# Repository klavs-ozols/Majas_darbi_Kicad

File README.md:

# Majas_darbi_Kicad
Šī ir mape, kur būs majasdarbi.

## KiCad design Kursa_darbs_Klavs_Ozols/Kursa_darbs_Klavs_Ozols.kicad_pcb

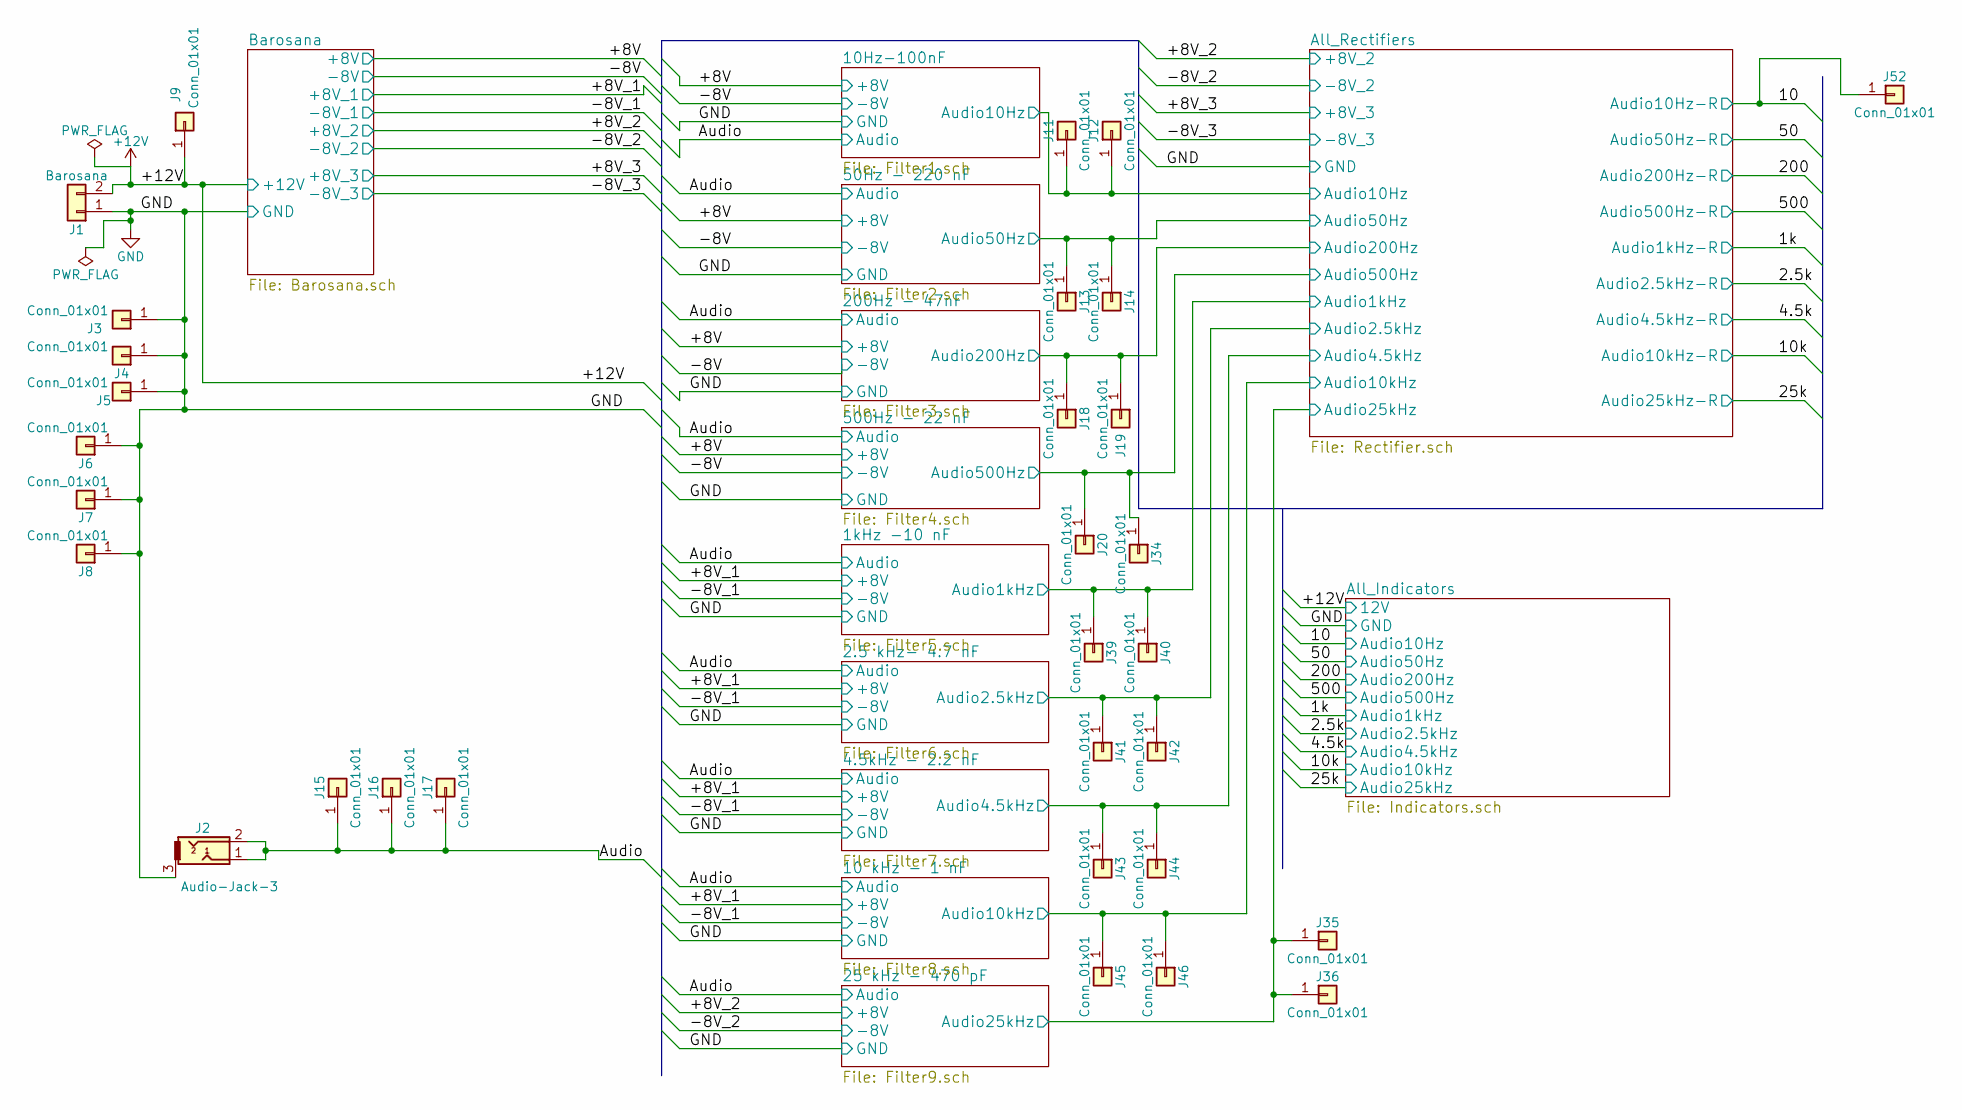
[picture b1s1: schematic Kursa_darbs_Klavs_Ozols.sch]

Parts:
J1: Barosana; BARREL_JACK
J2: Audio-Jack-3; Audio_Jack_3.5_mm_Stereo
J3, J4, J5, J6, J7, J8: Conn_01x01; MountingHole_3.2mm_M3_Pad_Via
J9, J11, J12, J13, J14, J15, J16, J17, J18, J19, J20, J34, J35, J36, J39, J40, J41, J42, J43, J44, J45, J46, J52: Conn_01x01; Measurement_Point_Round-TH_Small

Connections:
+12V: J1.2, J9.1; also elsewhere on the board
/1kHz -10 nF/Audio1kHz: J39.1, J40.1; also elsewhere on the board
/2.5 kHz- 4.7 nF/Audio2.5kHz: J41.1, J42.1; also elsewhere on the board
/4.5kHz - 2.2 nF/Audio4.5kHz: J43.1, J44.1; also elsewhere on the board
/10: J52.1; also elsewhere on the board
/10 kHz - 1 nF/Audio10kHz: J45.1, J46.1; also elsewhere on the board
/10Hz-100nF/Audio10Hz: J11.1, J12.1; also elsewhere on the board
/25 kHz - 470 pF/Audio25kHz: J35.1, J36.1; also elsewhere on the board
/50Hz - 220 nF/Audio50Hz: J13.1, J14.1; also elsewhere on the board
/200Hz - 47nF/Audio200Hz: J18.1, J19.1; also elsewhere on the board
/500Hz - 22 nF/Audio500Hz: J20.1, J34.1; also elsewhere on the board
/Audio: J2.1, J2.2, J15.1, J16.1, J17.1; also elsewhere on the board
GND: J1.1, J2.3, J3.1, J4.1, J5.1, J6.1, J7.1, J8.1; also elsewhere on the board

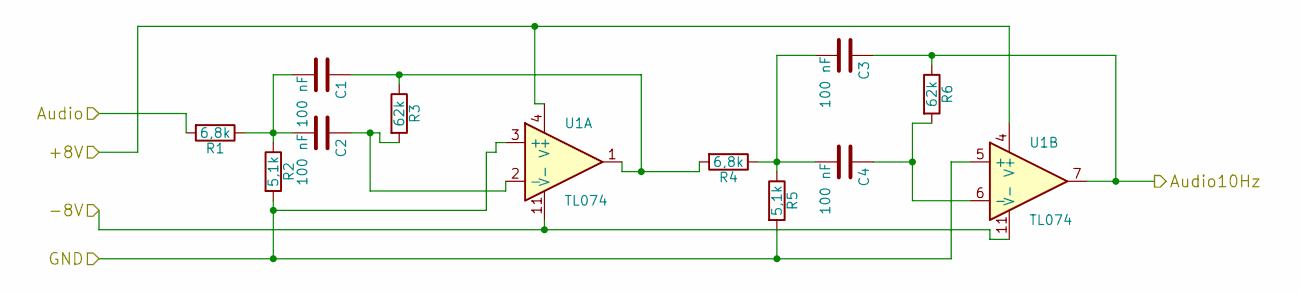
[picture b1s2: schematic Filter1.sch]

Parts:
C1, C2, C3, C4: 100 nF
R1, R4: 6,8k
R2, R5: 5,1k
R3, R6: 62k
U1: TL074

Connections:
/10Hz-100nF/Audio10Hz: C3.1, R6.1, U1.7; also elsewhere on the board
/+8V: U1.4 (V+); also elsewhere on the board
/-8V: U1.11 (V-); also elsewhere on the board
/Audio: R1.2; also elsewhere on the board
GND: R2.2, R5.2, U1.3 (+), U1.5 (+); also elsewhere on the board
unnamed: C1.1, R3.1, R4.2, U1.1
unnamed: C1.2, C2.2, R1.1, R2.1
unnamed: C2.1, R3.2, U1.2 (-)
unnamed: C3.2, C4.2, R4.1, R5.1
unnamed: C4.1, R6.2, U1.6 (-)

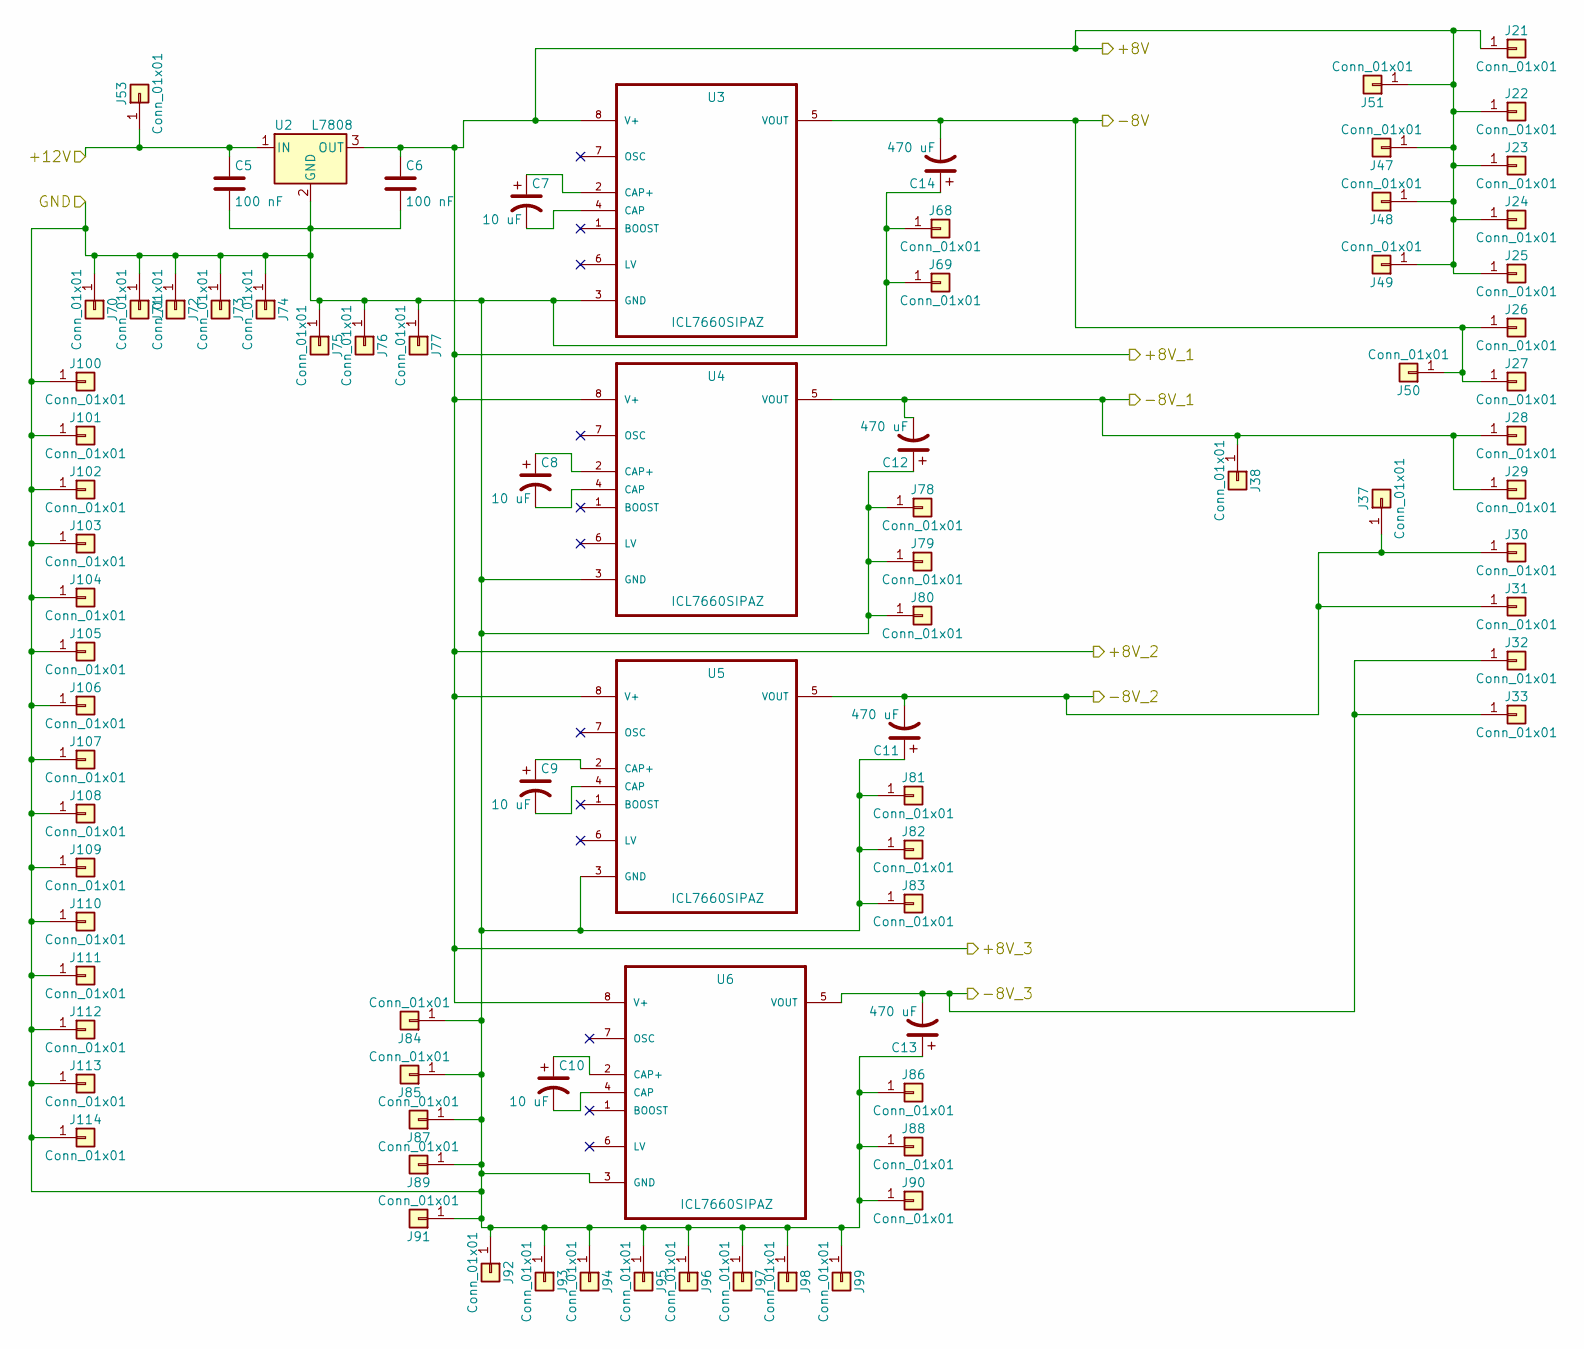
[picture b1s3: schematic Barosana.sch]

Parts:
C5, C6: 100 nF; C_1210_HandSoldering
C7, C8, C9, C10: 10 uF; CP_Elec_4x5.8
C11, C12, C13, C14: 470 uF; CP_Elec_10x10.5
J21, J22, J23, J24, J25, J26, J27, J28, J29, J30, J31, J32, J33, J37, J38, J47, J48, J49, J50, J51, J53, J68, J69, J70, J71, J72, J73, J74, J75, J76, J77, J78, J79, J80, J81, J82, J83, J84, J85, J86, J87, J88, J89, J90, J91, J92, J93, J94, J95, J96, J97, J98, J99, J100, J101, J102, J103, J104, J105, J106, J107, J108, J109, J110, J111, J112, J113, J114: Conn_01x01; Measurement_Point_Round-TH_Small
U2: L7808; TO-220_Vertical
U3, U4, U5, U6: ICL7660SIPAZ; SOIC-8_3.9x4.9mm_Pitch1.27mm

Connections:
+12V: C5.1, J53.1, U2.1 (IN); also elsewhere on the board
/+8V: C6.1, J21.1, J22.1, J23.1, J24.1, J25.1, J47.1, J48.1, J49.1, J51.1, U2.3 (OUT), U3.8 (V+), U4.8 (V+), U5.8 (V+), U6.8 (V+); also elsewhere on the board
/-8V: C14.2, J26.1, J27.1, J50.1, U3.5 (VOUT); also elsewhere on the board
/-8V_1: C12.2, J28.1, J29.1, J38.1, U4.5 (VOUT); also elsewhere on the board
GND: C5.2, C6.2, C11.1, C12.1, C13.1, C14.1, J68.1, J69.1, J70.1, J71.1, J72.1, J73.1, J74.1, J75.1, J76.1, J77.1, J78.1, J79.1, J80.1, J81.1, J82.1, J83.1, J84.1, J85.1, J86.1, J87.1, J88.1, J89.1, J90.1, J91.1, J92.1, J93.1, J94.1, J95.1, J96.1, J97.1, J98.1, J99.1, J100.1, J101.1, J102.1, J103.1, J104.1, J105.1, J106.1, J107.1, J108.1, J109.1, J110.1, J111.1, J112.1, J113.1, J114.1, U2.2 (GND), U3.3 (GND), U4.3 (GND), U5.3 (GND), U6.3 (GND); also elsewhere on the board
unnamed: C7.1, U3.2 (CAP+)
unnamed: C7.2, U3.4 (CAP)
unnamed: C8.1, U4.2 (CAP+)
unnamed: C8.2, U4.4 (CAP)
unnamed: C9.1, U5.2 (CAP+)
unnamed: C9.2, U5.4 (CAP)
unnamed: C10.1, U6.2 (CAP+)
unnamed: C10.2, U6.4 (CAP)

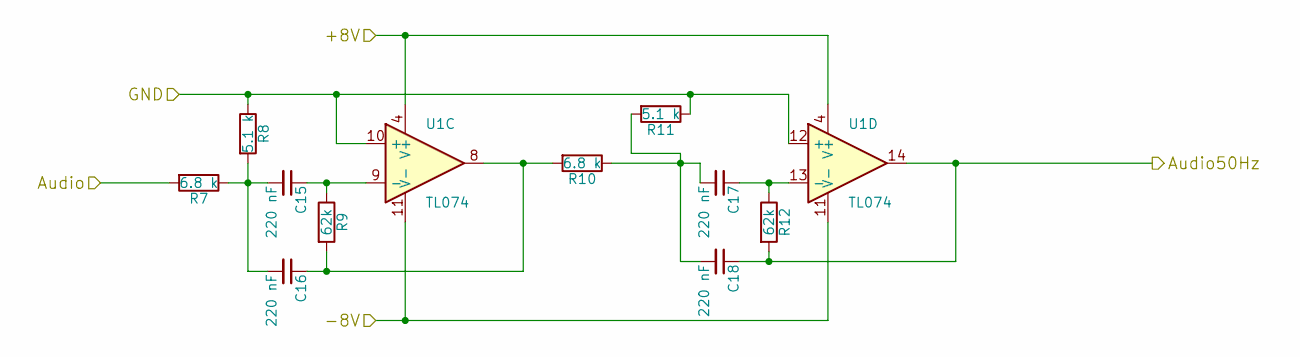
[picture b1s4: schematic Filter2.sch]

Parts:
C15, C16, C17, C18: 220 nF; C_Axial_L5.1mm_D3.1mm_P10.00mm_Horizontal
R7, R10: 6.8 k; R_Axial_DIN0309_L9.0mm_D3.2mm_P5.08mm_Vertical
R8, R11: 5.1 k; R_Axial_DIN0309_L9.0mm_D3.2mm_P5.08mm_Vertical
R9, R12: 62k; R_Axial_DIN0309_L9.0mm_D3.2mm_P5.08mm_Vertical
U1: TL074; DIL14

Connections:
/50Hz - 220 nF/Audio50Hz: C18.1, R12.2, U1.14; also elsewhere on the board
/+8V: U1.4 (V+); also elsewhere on the board
/-8V: U1.11 (V-); also elsewhere on the board
/Audio: R7.2; also elsewhere on the board
GND: R8.1, R11.1, U1.10 (+), U1.12 (+); also elsewhere on the board
unnamed: C15.1, R9.1, U1.9 (-)
unnamed: C15.2, C16.2, R7.1, R8.2
unnamed: C16.1, R9.2, R10.2, U1.8
unnamed: C17.1, R12.1, U1.13 (-)
unnamed: C17.2, C18.2, R10.1, R11.2

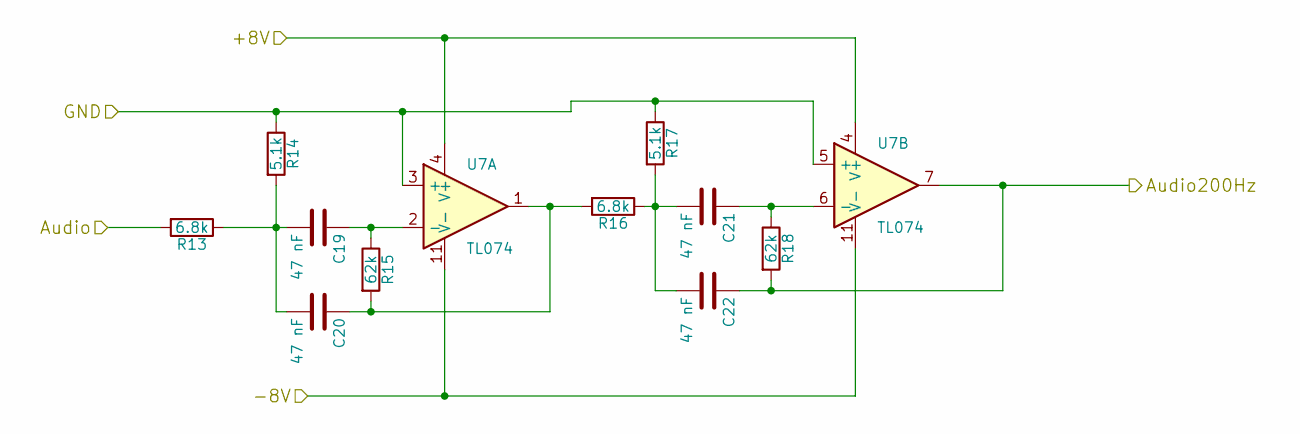
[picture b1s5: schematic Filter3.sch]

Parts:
C19, C20, C21, C22: 47 nF; C_Axial_L5.1mm_D3.1mm_P10.00mm_Horizontal
R13, R16: 6.8k; R_Axial_DIN0309_L9.0mm_D3.2mm_P5.08mm_Vertical
R14, R17: 5.1k; R_Axial_DIN0309_L9.0mm_D3.2mm_P5.08mm_Vertical
R15, R18: 62k; R_Axial_DIN0309_L9.0mm_D3.2mm_P5.08mm_Vertical
U7: TL074; DIL14

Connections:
/200Hz - 47nF/Audio200Hz: C22.1, R18.2, U7.7; also elsewhere on the board
/+8V: U7.4 (V+); also elsewhere on the board
/-8V: U7.11 (V-); also elsewhere on the board
/Audio: R13.2; also elsewhere on the board
GND: R14.1, R17.1, U7.3 (+), U7.5 (+); also elsewhere on the board
unnamed: C19.1, R15.1, U7.2 (-)
unnamed: C19.2, C20.2, R13.1, R14.2
unnamed: C20.1, R15.2, R16.2, U7.1
unnamed: C21.1, R18.1, U7.6 (-)
unnamed: C21.2, C22.2, R16.1, R17.2

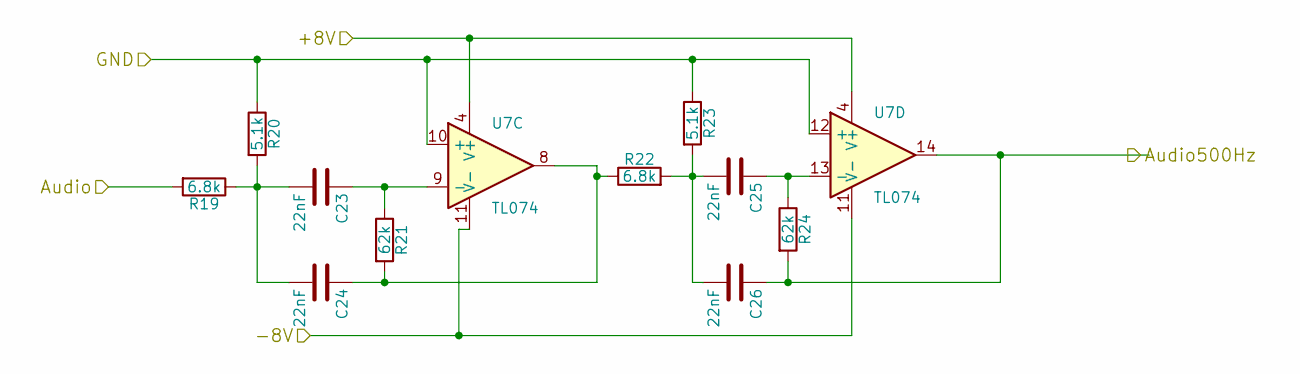
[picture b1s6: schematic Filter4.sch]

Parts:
C23, C24, C25, C26: 22nF; C_0805_HandSoldering
R19, R22: 6.8k; R_0805_HandSoldering
R20, R23: 5.1k; R_0805_HandSoldering
R21, R24: 62k; R_0805_HandSoldering
U7: TL074; SO14

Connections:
/500Hz - 22 nF/Audio500Hz: C26.1, R24.2, U7.14; also elsewhere on the board
/+8V: U7.4 (V+); also elsewhere on the board
/-8V: U7.11 (V-); also elsewhere on the board
/Audio: R19.2; also elsewhere on the board
GND: R20.1, R23.1, U7.10 (+), U7.12 (+); also elsewhere on the board
unnamed: C23.1, R21.1, U7.9 (-)
unnamed: C23.2, C24.2, R19.1, R20.2
unnamed: C24.1, R21.2, R22.1, U7.8
unnamed: C25.1, R24.1, U7.13 (-)
unnamed: C25.2, C26.2, R22.2, R23.2

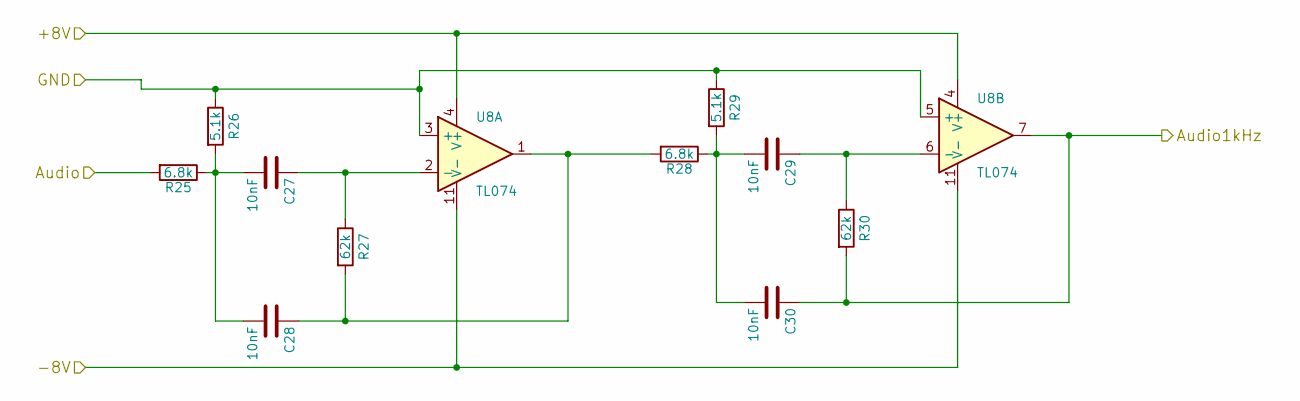
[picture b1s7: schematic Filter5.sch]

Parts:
C27, C28, C29, C30: 10nF; C_0805_HandSoldering
R25, R28: 6.8k; R_0805_HandSoldering
R26, R29: 5.1k; R_0805_HandSoldering
R27, R30: 62k; R_0805_HandSoldering
U8: TL074; SO14

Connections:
/1kHz -10 nF/Audio1kHz: C30.1, R30.2, U8.7; also elsewhere on the board
/+8V: U8.4 (V+); also elsewhere on the board
/-8V_1: U8.11 (V-); also elsewhere on the board
/Audio: R25.2; also elsewhere on the board
GND: R26.1, R29.1, U8.3 (+), U8.5 (+); also elsewhere on the board
unnamed: C27.1, R27.1, U8.2 (-)
unnamed: C27.2, C28.2, R25.1, R26.2
unnamed: C28.1, R27.2, R28.2, U8.1
unnamed: C29.1, R30.1, U8.6 (-)
unnamed: C29.2, C30.2, R28.1, R29.2

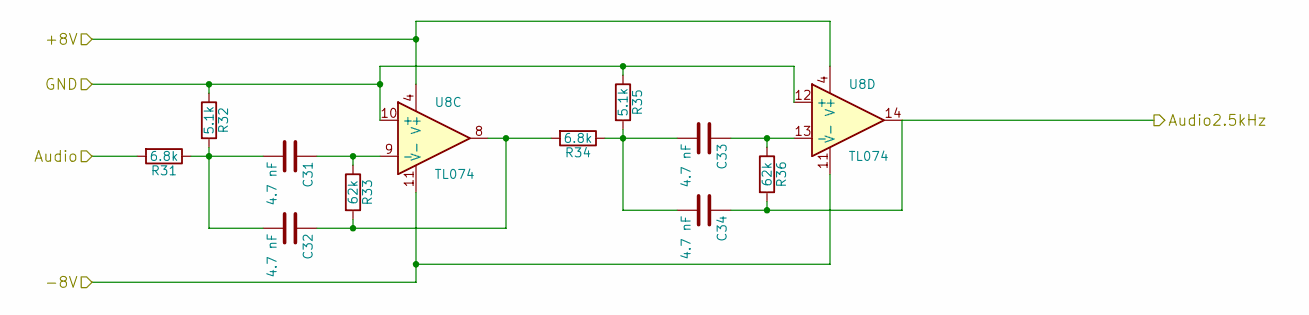
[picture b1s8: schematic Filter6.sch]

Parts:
C31, C32, C33, C34: 4.7 nF; C_Axial_L5.1mm_D3.1mm_P10.00mm_Horizontal
R31, R34: 6.8k; R_Axial_DIN0309_L9.0mm_D3.2mm_P5.08mm_Vertical
R32, R35: 5.1k; R_Axial_DIN0309_L9.0mm_D3.2mm_P5.08mm_Vertical
R33, R36: 62k; R_Axial_DIN0309_L9.0mm_D3.2mm_P5.08mm_Vertical
U8: TL074; DIL14

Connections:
/2.5 kHz- 4.7 nF/Audio2.5kHz: C34.1, R36.2, U8.14; also elsewhere on the board
/+8V: U8.4 (V+); also elsewhere on the board
/-8V_1: U8.11 (V-); also elsewhere on the board
/Audio: R31.2; also elsewhere on the board
GND: R32.1, R35.1, U8.10 (+), U8.12 (+); also elsewhere on the board
unnamed: C31.1, R33.1, U8.9 (-)
unnamed: C31.2, C32.2, R31.1, R32.2
unnamed: C32.1, R33.2, R34.2, U8.8
unnamed: C33.1, R36.1, U8.13 (-)
unnamed: C33.2, C34.2, R34.1, R35.2

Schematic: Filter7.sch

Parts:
C35, C36, C37, C38: 2.2nF; C_Axial_L5.1mm_D3.1mm_P10.00mm_Horizontal
R37, R40: 6.8k; R_Axial_DIN0309_L9.0mm_D3.2mm_P5.08mm_Vertical
R38, R41: 5.1k; R_Axial_DIN0309_L9.0mm_D3.2mm_P5.08mm_Vertical
R39, R42: 62k; R_Axial_DIN0309_L9.0mm_D3.2mm_P5.08mm_Vertical
U9: TL074; DIL14

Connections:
/4.5kHz - 2.2 nF/Audio4.5kHz: C38.1, R42.1, U9.7; also elsewhere on the board
/+8V: U9.4 (V+); also elsewhere on the board
/-8V_1: U9.11 (V-); also elsewhere on the board
/Audio: R37.2; also elsewhere on the board
GND: R38.1, R41.1, U9.3 (+), U9.5 (+); also elsewhere on the board
unnamed: C35.1, R39.2, U9.2 (-)
unnamed: C35.2, C36.2, R37.1, R38.2
unnamed: C36.1, R39.1, R40.2, U9.1
unnamed: C37.1, R42.2, U9.6 (-)
unnamed: C37.2, C38.2, R40.1, R41.2

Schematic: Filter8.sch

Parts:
C39, C40, C41, C42: 1nF; C_0805_HandSoldering
R43, R46: 6.8k; R_0805_HandSoldering
R44, R47: 5.1k; R_0805_HandSoldering
R45, R48: 62k; R_0805_HandSoldering
U9: TL074; SO14

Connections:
/10 kHz - 1 nF/Audio10kHz: C42.1, R48.2, U9.14; also elsewhere on the board
/+8V: U9.4 (V+); also elsewhere on the board
/-8V_1: U9.11 (V-); also elsewhere on the board
/Audio: R43.2; also elsewhere on the board
GND: R44.1, R47.1, U9.10 (+), U9.12 (+); also elsewhere on the board
unnamed: C39.1, R45.1, U9.9 (-)
unnamed: C39.2, C40.2, R43.1, R44.2
unnamed: C40.1, R45.2, R46.2, U9.8
unnamed: C41.1, R48.1, U9.13 (-)
unnamed: C41.2, C42.2, R46.1, R47.2

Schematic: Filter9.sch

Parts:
C43, C44, C45, C46: 470 pF; C_0805_HandSoldering
R49, R52: 6.8k; R_0805_HandSoldering
R50, R53: 5.1k; R_0805_HandSoldering
R51, R54: 62k; R_0805_HandSoldering
U10: TL074; SO14

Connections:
/25 kHz - 470 pF/Audio25kHz: C46.1, R54.1, U10.7; also elsewhere on the board
/+8V: U10.4 (V+); also elsewhere on the board
/Audio: R49.2; also elsewhere on the board
GND: R50.1, R53.1, U10.3 (+), U10.5 (+); also elsewhere on the board
unnamed: C43.1, R51.1, U10.2 (-)
unnamed: C43.2, C44.2, R49.1, R50.2
unnamed: C44.1, R51.2, R52.2, U10.1
unnamed: C45.1, R54.2, U10.6 (-)
unnamed: C45.2, C46.2, R52.1, R53.2

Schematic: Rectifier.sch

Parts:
C47, C48, C49, C50, C51, C52, C53, C54, C55, C56, C57, C58, C59, C60, C61, C62, C63, C64: 1 uF; C_0805_HandSoldering
D1, D2, D3, D4, D5, D6, D7, D8, D9, D10, D11, D12, D13, D14, D15, D16, D17, D18: 1N4148; DIOMELF3515N
R55, R56, R57, R58, R71, R72, R73, R83, R84: 22k; R_0805_HandSoldering
R59, R60, R61, R62, R74, R75, R76, R85, R86: 220k; R_0805_HandSoldering
R63, R64, R65, R66, R77, R78, R79, R87, R88: 1k; R_0805_HandSoldering
R67, R68, R69, R70, R80, R81, R82, R89, R90: 47k; R_0805_HandSoldering
U10, U11, U12: TL074; SO14

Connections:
/1k: C58.1, R77.1, R80.1; also elsewhere on the board
/1kHz -10 nF/Audio1kHz: C55.2; also elsewhere on the board
/2.5 kHz- 4.7 nF/Audio2.5kHz: C56.2; also elsewhere on the board
/2.5k: C59.1, R78.1, R81.1; also elsewhere on the board
/4.5k: C60.1, R79.1, R82.1; also elsewhere on the board
/4.5kHz - 2.2 nF/Audio4.5kHz: C57.2; also elsewhere on the board
/10: C51.1, R63.1, R67.1; also elsewhere on the board
/10 kHz - 1 nF/Audio10kHz: C61.2; also elsewhere on the board
/10Hz-100nF/Audio10Hz: C47.2; also elsewhere on the board
/10k: C63.1, R87.1, R89.1; also elsewhere on the board
/25 kHz - 470 pF/Audio25kHz: C62.2; also elsewhere on the board
/25k: C64.1, R88.1, R90.1; also elsewhere on the board
/50: C52.1, R64.1, R68.1; also elsewhere on the board
/50Hz - 220 nF/Audio50Hz: C48.2; also elsewhere on the board
/200: C54.1, R66.1, R70.1; also elsewhere on the board
/200Hz - 47nF/Audio200Hz: C50.2; also elsewhere on the board
/500: C53.1, R65.1, R69.1; also elsewhere on the board
/500Hz - 22 nF/Audio500Hz: C49.2; also elsewhere on the board
/+8V: U10.4 (V+), U11.4 (V+), U12.4 (V+); also elsewhere on the board
GND: C51.2, C52.2, C53.2, C54.2, C58.2, C59.2, C60.2, C63.2, C64.2, R67.2, R68.2, R69.2, R70.2, R80.2, R81.2, R82.2, R89.2, R90.2, U10.10 (+), U10.12 (+), U11.3 (+), U11.5 (+), U11.10 (+), U11.12 (+), U12.3 (+), U12.5 (+), U12.10 (+); also elsewhere on the board
unnamed: C47.1, R55.2
unnamed: C48.1, R56.2
unnamed: C49.1, R57.2
unnamed: C50.1, R58.2
unnamed: C55.1, R71.2
unnamed: C56.1, R72.2
unnamed: C57.1, R73.2
unnamed: C61.1, R83.2
unnamed: C62.1, R84.2
unnamed: D1.A, R55.1, R59.2, U10.9 (-)
unnamed: D1.C, D5.A, U10.8
unnamed: D2.A, R56.1, R60.2, U10.13 (-)
unnamed: D2.C, D3.A, U10.14
unnamed: D3.C, R60.1, R64.2
unnamed: D4.A, R57.1, R61.2, U11.2 (-)
unnamed: D4.C, D7.A, U11.1
unnamed: D5.C, R59.1, R63.2
unnamed: D6.A, R58.1, R62.2, U11.6 (-)
unnamed: D6.C, D8.A, U11.7
unnamed: D7.C, R61.1, R65.2
unnamed: D8.C, R62.1, R66.2
unnamed: D9.A, R71.1, R74.2, U11.9 (-)
unnamed: D10.A, R72.1, R75.2, U11.13 (-)
unnamed: D10.C, D13.A, U11.14
unnamed: D11.A, R73.1, R76.2, U12.2 (-)
unnamed: D11.C, D14.A, U12.1
unnamed: D9.C, D12.A, U11.8
unnamed: D12.C, R74.1, R77.2
unnamed: D13.C, R75.1, R78.2
unnamed: D14.C, R76.1, R79.2
unnamed: D15.A, R83.1, R85.2, U12.6 (-)
unnamed: D15.C, D17.A, U12.7
unnamed: D16.A, R84.1, R86.2, U12.9 (-)
unnamed: D16.C, D18.A, U12.8
unnamed: D17.C, R85.1, R87.2
unnamed: D18.C, R86.1, R88.2

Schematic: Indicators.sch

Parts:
C65: 10 uF; CP_Elec_10x10.5
C66: 10uF; CP_Elec_10x10.5
D19, D20, D21, D22, D23, D24, D25, D26, D27, D28, D29, D30, D31, D32, D33, D34, D35, D36, D37, D38, D39, D40, D41, D42, D43, D44, D45, D46, D47, D48, D49, D50, D51, D52, D53, D54, D55, D56, D57, D58, D59, D60, D61, D62, D63, D64, D65, D66, D67, D68, D69, D70, D71, D72, D73, D74, D75, D76, D77, D78: LED; LED_D5.0mm
R91, R92, R93, R94, R95, R96: 1.2k; R_0805_HandSoldering
R97: 240; R_0805_HandSoldering
RV1, RV2, RV3, RV4, RV5, RV6, RV8, RV9, RV10, RV11, RV16: 10k; Potentiometer_Trimmer_Vishay_TS53YJ
RV7, RV12: 4.7k; Potentiometer_Trimmer_Vishay_TS53YJ
U13: LM3915; DIP-18_W7.62mm_LongPads
U14, U15, U16, U17, U18: LM3915; DIP-18_W7.62mm_Socket
U19: LM317_TO3; TO-220_Vertical

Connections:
+12V: C66.1, U13.3 (V+), U13.9 (MODE), U14.3 (V+), U14.9 (MODE), U15.3 (V+), U15.9 (MODE), U16.3 (V+), U16.9 (MODE), U17.3 (V+), U17.9 (MODE), U18.3 (V+), U18.9 (MODE), U19.2 (VI); also elsewhere on the board
/1k: U16.5 (SIG); also elsewhere on the board
/2.5k: U18.5 (SIG); also elsewhere on the board
/10: U13.5 (SIG); also elsewhere on the board
/50: U15.5 (SIG); also elsewhere on the board
/200: U17.5 (SIG); also elsewhere on the board
/500: U14.5 (SIG); also elsewhere on the board
/All_Indicators/Turpinajums/LED_Supply: C65.1, D19.2 (A), D20.2 (A), D21.2 (A), D22.2 (A), D23.2 (A), D24.2 (A), D25.2 (A), D26.2 (A), D27.2 (A), D28.2 (A), D29.2 (A), D30.2 (A), D31.2 (A), D32.2 (A), D33.2 (A), D34.2 (A), D35.2 (A), D36.2 (A), D37.2 (A), D38.2 (A), D39.2 (A), D40.2 (A), D41.2 (A), D42.2 (A), D43.2 (A), D44.2 (A), D45.2 (A), D46.2 (A), D47.2 (A), D48.2 (A), D49.2 (A), D50.2 (A), D51.2 (A), D52.2 (A), D53.2 (A), D54.2 (A), D55.2 (A), D56.2 (A), D57.2 (A), D58.2 (A), D59.2 (A), D60.2 (A), D61.2 (A), D62.2 (A), D63.2 (A), D64.2 (A), D65.2 (A), D66.2 (A), D67.2 (A), D68.2 (A), D69.2 (A), D70.2 (A), D71.2 (A), D72.2 (A), D73.2 (A), D74.2 (A), D75.2 (A), D76.2 (A), D77.2 (A), D78.2 (A), R97.2, U19.3 (VO); also elsewhere on the board
GND: C65.2, C66.2, RV1.1, RV2.1, RV3.3, RV4.3, RV5.1, RV6.3, RV7.3, RV8.1, RV9.1, RV10.3, RV11.3, RV12.1, RV12.2, RV16.1, U13.2 (V-), U14.2 (V-), U15.2 (V-), U16.2 (V-), U17.2 (V-), U18.2 (V-); also elsewhere on the board
unnamed: D19.1 (K), U13.1 (LED1)
unnamed: D20.1 (K), U14.1 (LED1)
unnamed: D21.1 (K), U13.18 (LED2)
unnamed: D22.1 (K), U14.18 (LED2)
unnamed: D23.1 (K), U13.17 (LED3)
unnamed: D24.1 (K), U14.17 (LED3)
unnamed: D25.1 (K), U13.16 (LED4)
unnamed: D26.1 (K), U14.16 (LED4)
unnamed: D27.1 (K), U13.15 (LED5)
unnamed: D28.1 (K), U14.15 (LED5)
unnamed: D29.1 (K), U13.14 (LED6)
unnamed: D30.1 (K), U14.14 (LED6)
unnamed: D31.1 (K), U13.13 (LED7)
unnamed: D32.1 (K), U14.13 (LED7)
unnamed: D33.1 (K), U13.12 (LED8)
unnamed: D34.1 (K), U14.12 (LED8)
unnamed: D35.1 (K), U13.11 (LED9)
unnamed: D36.1 (K), U14.11 (LED9)
unnamed: D37.1 (K), U13.10 (LED10)
unnamed: D38.1 (K), U14.10 (LED10)
unnamed: D39.1 (K), U15.1 (LED1)
unnamed: D40.1 (K), U16.1 (LED1)
unnamed: D41.1 (K), U15.18 (LED2)
unnamed: D42.1 (K), U16.18 (LED2)
unnamed: D43.1 (K), U15.17 (LED3)
unnamed: D44.1 (K), U16.17 (LED3)
unnamed: D45.1 (K), U15.16 (LED4)
unnamed: D46.1 (K), U16.16 (LED4)
unnamed: D47.1 (K), U15.15 (LED5)
unnamed: D48.1 (K), U16.15 (LED5)
unnamed: D49.1 (K), U15.14 (LED6)
unnamed: D50.1 (K), U16.14 (LED6)
unnamed: D51.1 (K), U15.13 (LED7)
unnamed: D52.1 (K), U16.13 (LED7)
unnamed: D53.1 (K), U15.12 (LED8)
unnamed: D54.1 (K), U16.12 (LED8)
unnamed: D55.1 (K), U15.11 (LED9)
unnamed: D56.1 (K), U16.11 (LED9)
unnamed: D57.1 (K), U15.10 (LED10)
unnamed: D58.1 (K), U16.10 (LED10)
unnamed: D59.1 (K), U17.1 (LED1)
unnamed: D60.1 (K), U18.1 (LED1)
unnamed: D61.1 (K), U17.18 (LED2)
unnamed: D62.1 (K), U18.18 (LED2)
unnamed: D63.1 (K), U17.17 (LED3)
unnamed: D64.1 (K), U18.17 (LED3)
unnamed: D65.1 (K), U17.16 (LED4)
unnamed: D66.1 (K), U18.16 (LED4)
unnamed: D67.1 (K), U17.15 (LED5)
unnamed: D68.1 (K), U18.15 (LED5)
unnamed: D69.1 (K), U17.14 (LED6)
unnamed: D70.1 (K), U18.14 (LED6)
unnamed: D71.1 (K), U17.13 (LED7)
unnamed: D72.1 (K), U18.13 (LED7)
unnamed: D73.1 (K), U17.12 (LED8)
unnamed: D74.1 (K), U18.12 (LED8)
unnamed: D75.1 (K), U17.11 (LED9)
unnamed: D76.1 (K), U18.11 (LED9)
unnamed: D77.1 (K), U17.10 (LED10)
unnamed: D78.1 (K), U18.10 (LED10)
unnamed: R91.1, U13.6 (R(HI)), U13.7 (REF(OUT))
unnamed: R91.2, RV3.1, RV3.2, U13.8 (REF(ADJ))
unnamed: R92.1, U14.6 (R(HI)), U14.7 (REF(OUT))
unnamed: R92.2, RV4.1, RV4.2, U14.8 (REF(ADJ))
unnamed: R93.1, U15.6 (R(HI)), U15.7 (REF(OUT))
unnamed: R93.2, RV6.1, RV6.2, U15.8 (REF(ADJ))
unnamed: R94.1, U16.6 (R(HI)), U16.7 (REF(OUT))
unnamed: R94.2, RV7.1, RV7.2, U16.8 (REF(ADJ))
unnamed: R95.1, U17.6 (R(HI)), U17.7 (REF(OUT))
unnamed: R95.2, RV10.1, RV10.2, U17.8 (REF(ADJ))
unnamed: R96.1, U18.6 (R(HI)), U18.7 (REF(OUT))
unnamed: R96.2, RV11.1, RV11.2, U18.8 (REF(ADJ))
unnamed: R97.1, RV12.3, U19.1 (ADJ)
unnamed: RV1.2, RV1.3, U14.4 (R(LO))
unnamed: RV2.2, RV2.3, U13.4 (R(LO))
unnamed: RV5.2, RV5.3, U15.4 (R(LO))
unnamed: RV8.2, RV8.3, U18.4 (R(LO))
unnamed: RV9.2, RV9.3, U17.4 (R(LO))
unnamed: RV16.2, RV16.3, U16.4 (R(LO))

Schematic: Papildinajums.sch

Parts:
D79, D80, D81, D82, D83, D84, D85, D86, D87, D88, D89, D90, D91, D92, D93, D94, D95, D96, D97, D98, D99, D100, D101, D102, D103, D104, D105, D106, D107, D108: LED; LED_D5.0mm
R98, R99, R100: 1.2k; R_Axial_DIN0309_L9.0mm_D3.2mm_P5.08mm_Vertical
RV13, RV14, RV15, RV17, RV18, RV19: 10k; Potentiometer_Trimmer_Vishay_T7YA_Horizontal
U20, U21, U22: LM3915; DIP-18_W7.62mm_LongPads

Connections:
+12V: U20.3 (V+), U20.9 (MODE), U21.3 (V+), U21.9 (MODE), U22.3 (V+), U22.9 (MODE); also elsewhere on the board
/4.5k: U21.5 (SIG); also elsewhere on the board
/10k: U20.5 (SIG); also elsewhere on the board
/25k: U22.5 (SIG); also elsewhere on the board
/All_Indicators/Turpinajums/LED_Supply: D79.2 (A), D80.2 (A), D81.2 (A), D82.2 (A), D83.2 (A), D84.2 (A), D85.2 (A), D86.2 (A), D87.2 (A), D88.2 (A), D89.2 (A), D90.2 (A), D91.2 (A), D92.2 (A), D93.2 (A), D94.2 (A), D95.2 (A), D96.2 (A), D97.2 (A), D98.2 (A), D99.2 (A), D100.2 (A), D101.2 (A), D102.2 (A), D103.2 (A), D104.2 (A), D105.2 (A), D106.2 (A), D107.2 (A), D108.2 (A); also elsewhere on the board
GND: RV13.1, RV14.1, RV15.1, RV17.1, RV18.1, RV19.1, U20.2 (V-), U21.2 (V-), U22.2 (V-); also elsewhere on the board
unnamed: D79.1 (K), U20.1 (LED1)
unnamed: D80.1 (K), U20.18 (LED2)
unnamed: D81.1 (K), U20.17 (LED3)
unnamed: D82.1 (K), U20.16 (LED4)
unnamed: D83.1 (K), U20.15 (LED5)
unnamed: D84.1 (K), U20.14 (LED6)
unnamed: D85.1 (K), U20.13 (LED7)
unnamed: D86.1 (K), U20.12 (LED8)
unnamed: D87.1 (K), U20.11 (LED9)
unnamed: D88.1 (K), U20.10 (LED10)
unnamed: D89.1 (K), U21.1 (LED1)
unnamed: D90.1 (K), U21.18 (LED2)
unnamed: D91.1 (K), U21.17 (LED3)
unnamed: D92.1 (K), U21.16 (LED4)
unnamed: D93.1 (K), U21.15 (LED5)
unnamed: D94.1 (K), U21.14 (LED6)
unnamed: D95.1 (K), U21.13 (LED7)
unnamed: D96.1 (K), U21.12 (LED8)
unnamed: D97.1 (K), U21.11 (LED9)
unnamed: D98.1 (K), U21.10 (LED10)
unnamed: D99.1 (K), U22.1 (LED1)
unnamed: D100.1 (K), U22.18 (LED2)
unnamed: D101.1 (K), U22.17 (LED3)
unnamed: D102.1 (K), U22.16 (LED4)
unnamed: D103.1 (K), U22.15 (LED5)
unnamed: D104.1 (K), U22.14 (LED6)
unnamed: D105.1 (K), U22.13 (LED7)
unnamed: D106.1 (K), U22.12 (LED8)
unnamed: D107.1 (K), U22.11 (LED9)
unnamed: D108.1 (K), U22.10 (LED10)
unnamed: R98.1, U20.6 (R(HI)), U20.7 (REF(OUT))
unnamed: R98.2, RV13.2, RV13.3, U20.8 (REF(ADJ))
unnamed: R99.1, U21.6 (R(HI)), U21.7 (REF(OUT))
unnamed: R99.2, RV14.2, RV14.3, U21.8 (REF(ADJ))
unnamed: R100.1, U22.6 (R(HI)), U22.7 (REF(OUT))
unnamed: R100.2, RV15.2, RV15.3, U22.8 (REF(ADJ))
unnamed: RV17.2, RV17.3, U20.4 (R(LO))
unnamed: RV18.2, RV18.3, U21.4 (R(LO))
unnamed: RV19.2, RV19.3, U22.4 (R(LO))

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
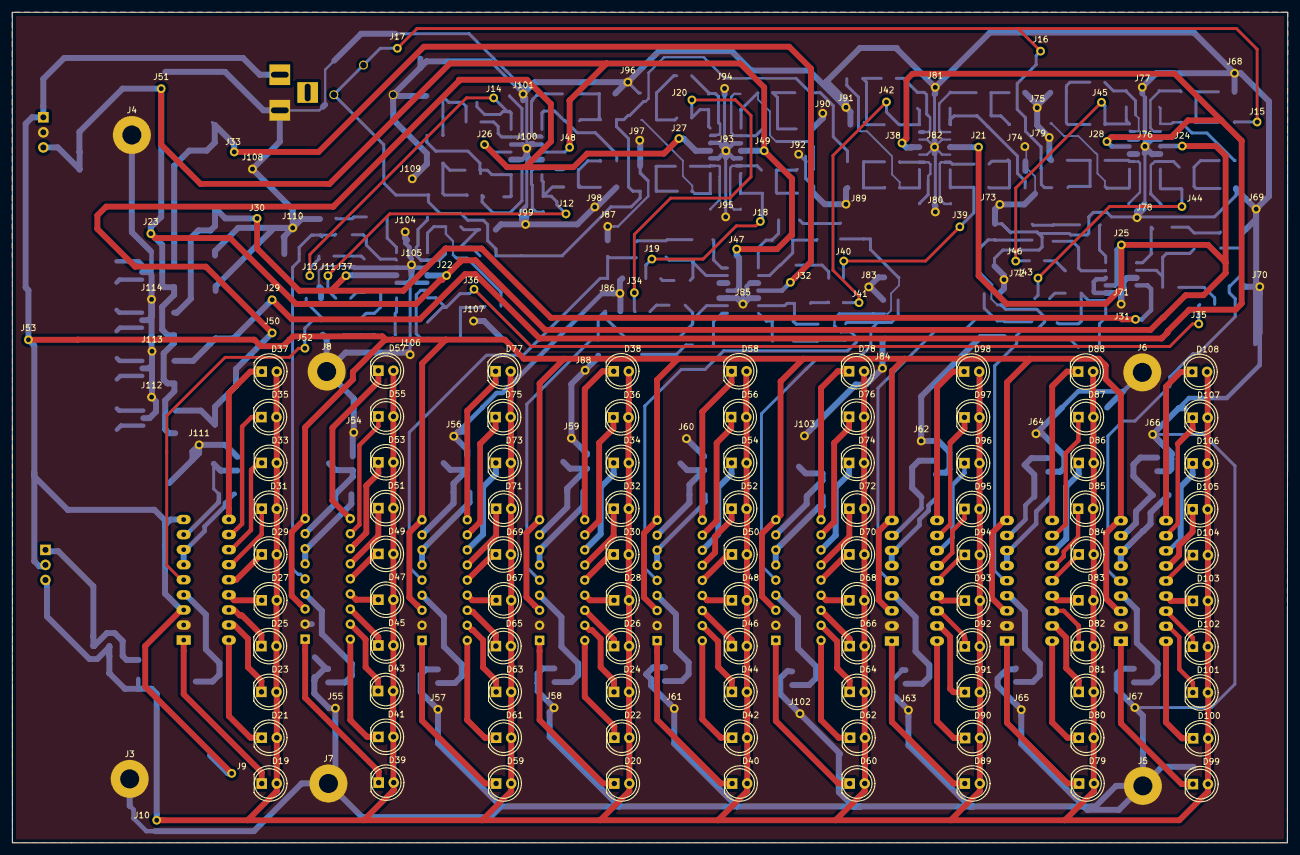
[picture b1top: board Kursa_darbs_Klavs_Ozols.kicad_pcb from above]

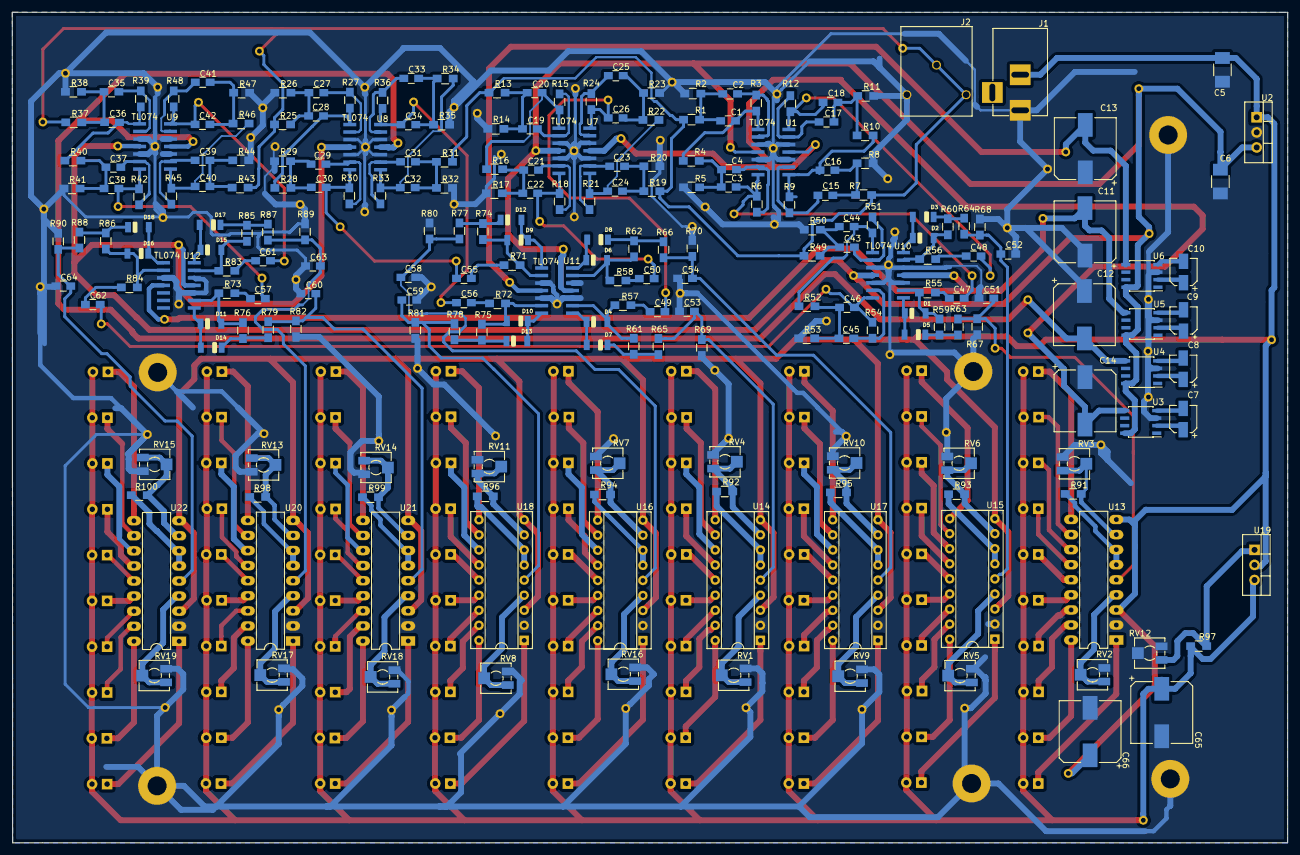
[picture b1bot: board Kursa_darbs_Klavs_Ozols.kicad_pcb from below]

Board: 4 copper layers, 215.0 x 140.0 mm, 429 parts (227 on the bottom side), 234 nets.

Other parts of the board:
J10, J54, J55, J56, J57, J58, J59, J60, J61, J62, J63, J64, J65, J66, J67: Conn_01x01; Measurement_Point_Round-TH_Small

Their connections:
/All_Indicators/Turpinajums/LED_Supply: J10.1; also elsewhere on the board
GND: J54.1, J55.1, J56.1, J57.1, J58.1, J59.1, J60.1, J61.1, J62.1, J63.1, J64.1, J65.1, J66.1, J67.1; also elsewhere on the board
